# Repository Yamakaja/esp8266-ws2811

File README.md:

# ESP8266-WS2811

## Requirements

* Linux (I've not tried other environments)
* The [esp-open-sdk](https://github.com/pfalcon/esp-open-sdk)
* An environment variable "ESP_ROOT" pointing to the root of the above sdk
* An addition to the `PATH` environment variable, pointing into `$ESP_ROOT/xtensa-lx106-elf/bin/`

## Setup

* Copy the user_config.h.template header to user_config.h (Within the `include/` directory) and enter your SSID and password.
* Get your hardware setup - the signal will be sent to the uart RX pin - see the KiCad project and schematic in `pcb/` for more information.
* Connect your ESP and find out which port it is connected to.
* Get your ESP ready for flashing over UART
* Comile and flash by running `make flash PORT=<esp>`, where `<esp>` would usually be something like `/dev/ttyUSB0`

## The protocol

You can then control the led strip by sending UDP packets with the following format:

    [Packet] 	:= [LED] * ledCount
    [LED]		:= [r: byte][g: byte][b: byte]

##### Example:

Set the first driver to magenta:

```java
byte[] packet = new byte[]{0xFF, 0x00, 0xFF};
```

## Timing

More timing information can be found in the [Timing](Timing) file

©2017 Yamakaja

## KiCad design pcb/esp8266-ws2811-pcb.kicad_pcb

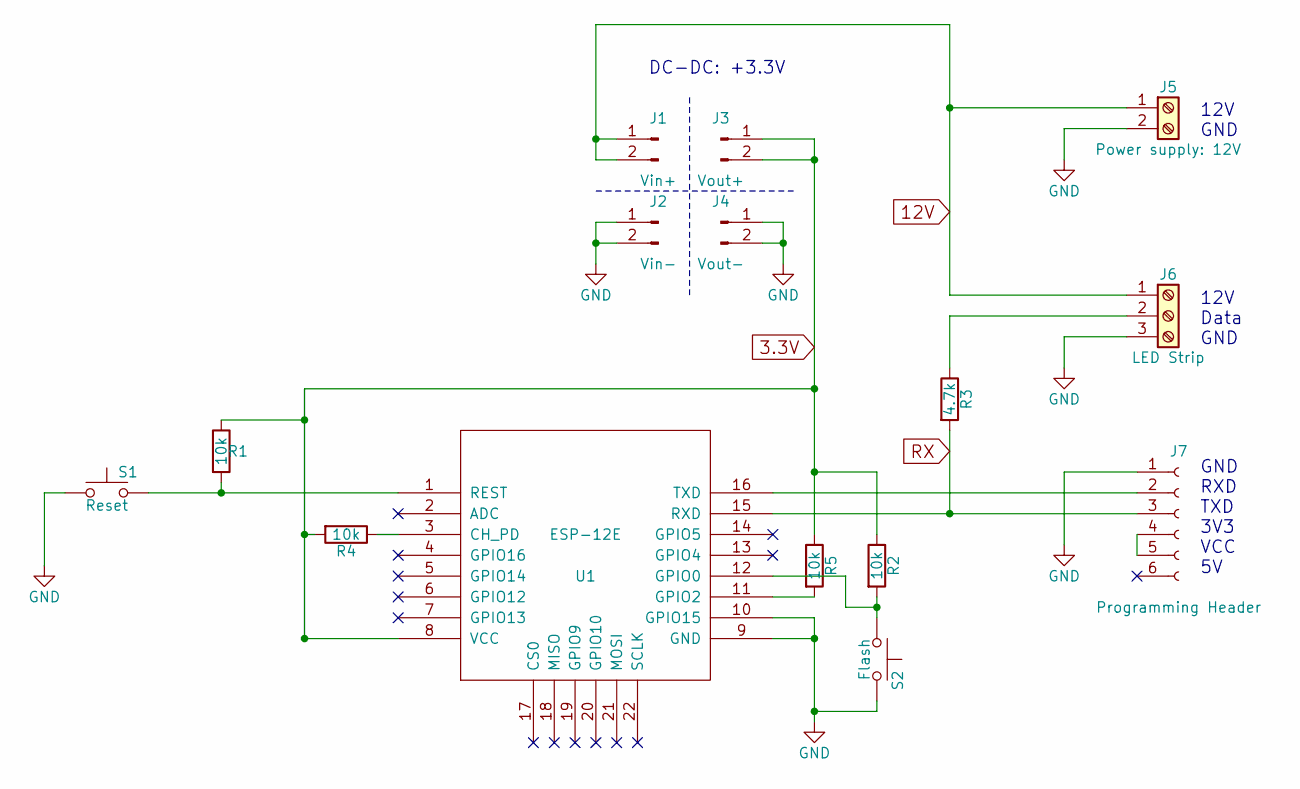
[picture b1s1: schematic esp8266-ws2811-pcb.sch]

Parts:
J1: Vin+; Pin_Header_Straight_1x02_Pitch2.54mm
J2: Vin-; Pin_Header_Straight_1x02_Pitch2.54mm
J3: Vout+; Pin_Header_Straight_1x02_Pitch2.54mm
J4: Vout-; Pin_Header_Straight_1x02_Pitch2.54mm
J5: Power supply: 12V; TerminalBlock_bornier-2_P5.08mm
J6: LED Strip; TerminalBlock_bornier-3_P5.08mm
J7: Programming Header; Socket_Strip_Straight_1x06_Pitch2.54mm
R1, R2, R4, R5: 10k; R_Axial_DIN0207_L6.3mm_D2.5mm_P7.62mm_Horizontal
R3: 4.7k; R_Axial_DIN0207_L6.3mm_D2.5mm_P7.62mm_Horizontal
S1: Reset; SW_PUSH_6mm_h7.3mm
S2: Flash; SW_PUSH_6mm_h7.3mm
U1: ESP-12E

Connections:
3.3V: J3.1, J3.2, R1.1, R2.1, R4.2, R5.1, U1.8 (VCC)
12V: J1.1, J1.2, J5.1, J6.1
GND: J2.1, J2.2, J4.1, J4.2, J5.2, J6.3, J7.1, S1.1, S2.2, U1.9 (GND), U1.10 (GPIO15)
unnamed: J6.2, R3.1
unnamed: J7.2, U1.16 (TXD)
unnamed: J7.4, J7.5
unnamed: R1.2, S1.2, U1.1 (REST)
unnamed: R2.2, S2.1, U1.12 (GPIO0)
unnamed: R4.1, U1.3 (CH_PD)
unnamed: R5.2, U1.11 (GPIO2)
RX: J7.3, R3.2, U1.15 (RXD)

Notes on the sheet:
GND RXD TXD 3V3 VCC 5V
DC-DC: +3.3V
12V Data GND
12V GND

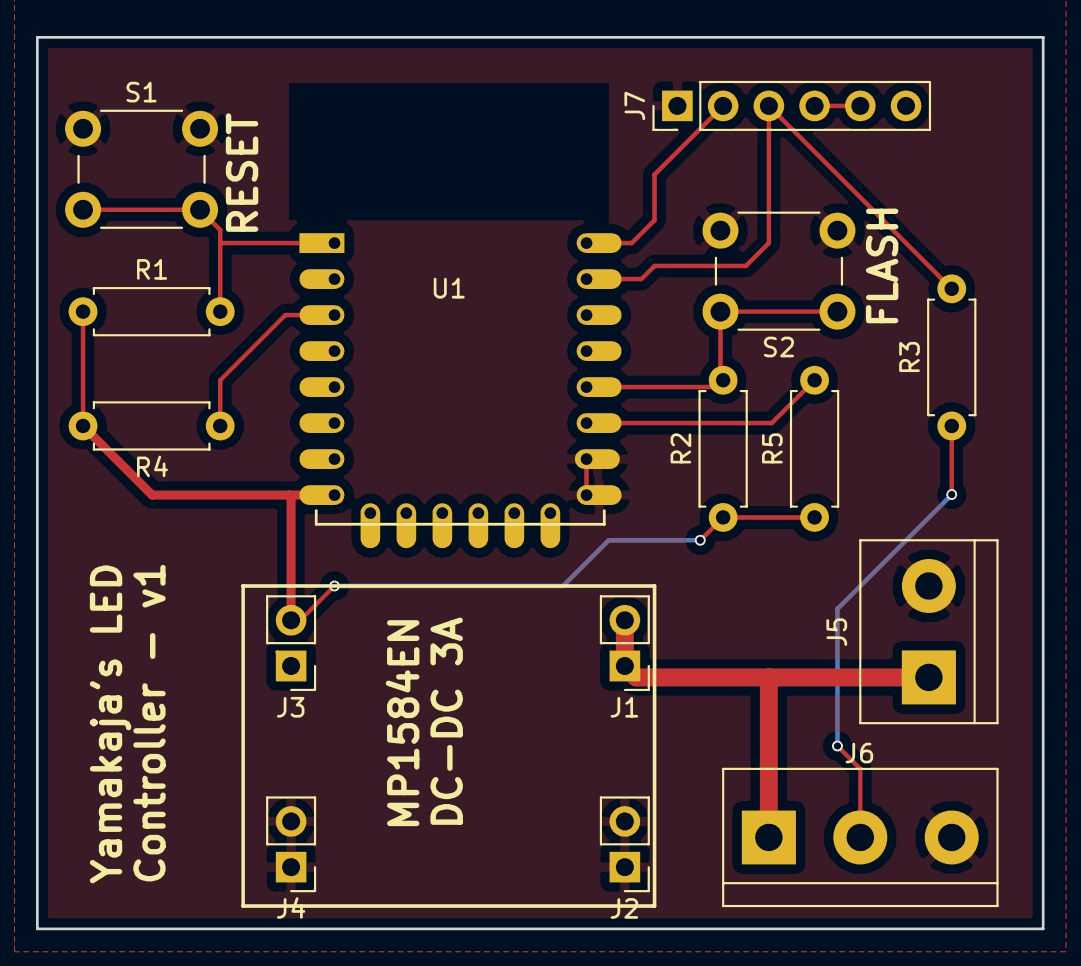
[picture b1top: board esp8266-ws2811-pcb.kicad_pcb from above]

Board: 2 copper layers, 55.9 x 49.5 mm, 15 parts (0 on the bottom side), 11 nets.

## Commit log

2017-03-26 "Remove" debug statements
2017-03-26 Add Readme
2018-03-28 Add PCB
2018-03-29 Switch to esp-open-sdk; Use I2C DMA
2018-03-29 Fix license
2018-03-29 Remove unused header
2018-03-30 Cleanup
2018-10-03 Fix multiple issues
